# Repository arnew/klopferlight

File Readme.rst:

Klopfer Light
=============

.. figure:: ./klopferlight.png

Inspired by https://www.printables.com/model/1125977-led-cap-for-small-bottles-with-m18-thread-for-ws28 and the Mate Light https://github.com/jaseg/matelight , this design aims to provide a draft for a 4x5 crate backplane.

To be followed up with some controller and firmware design ;)

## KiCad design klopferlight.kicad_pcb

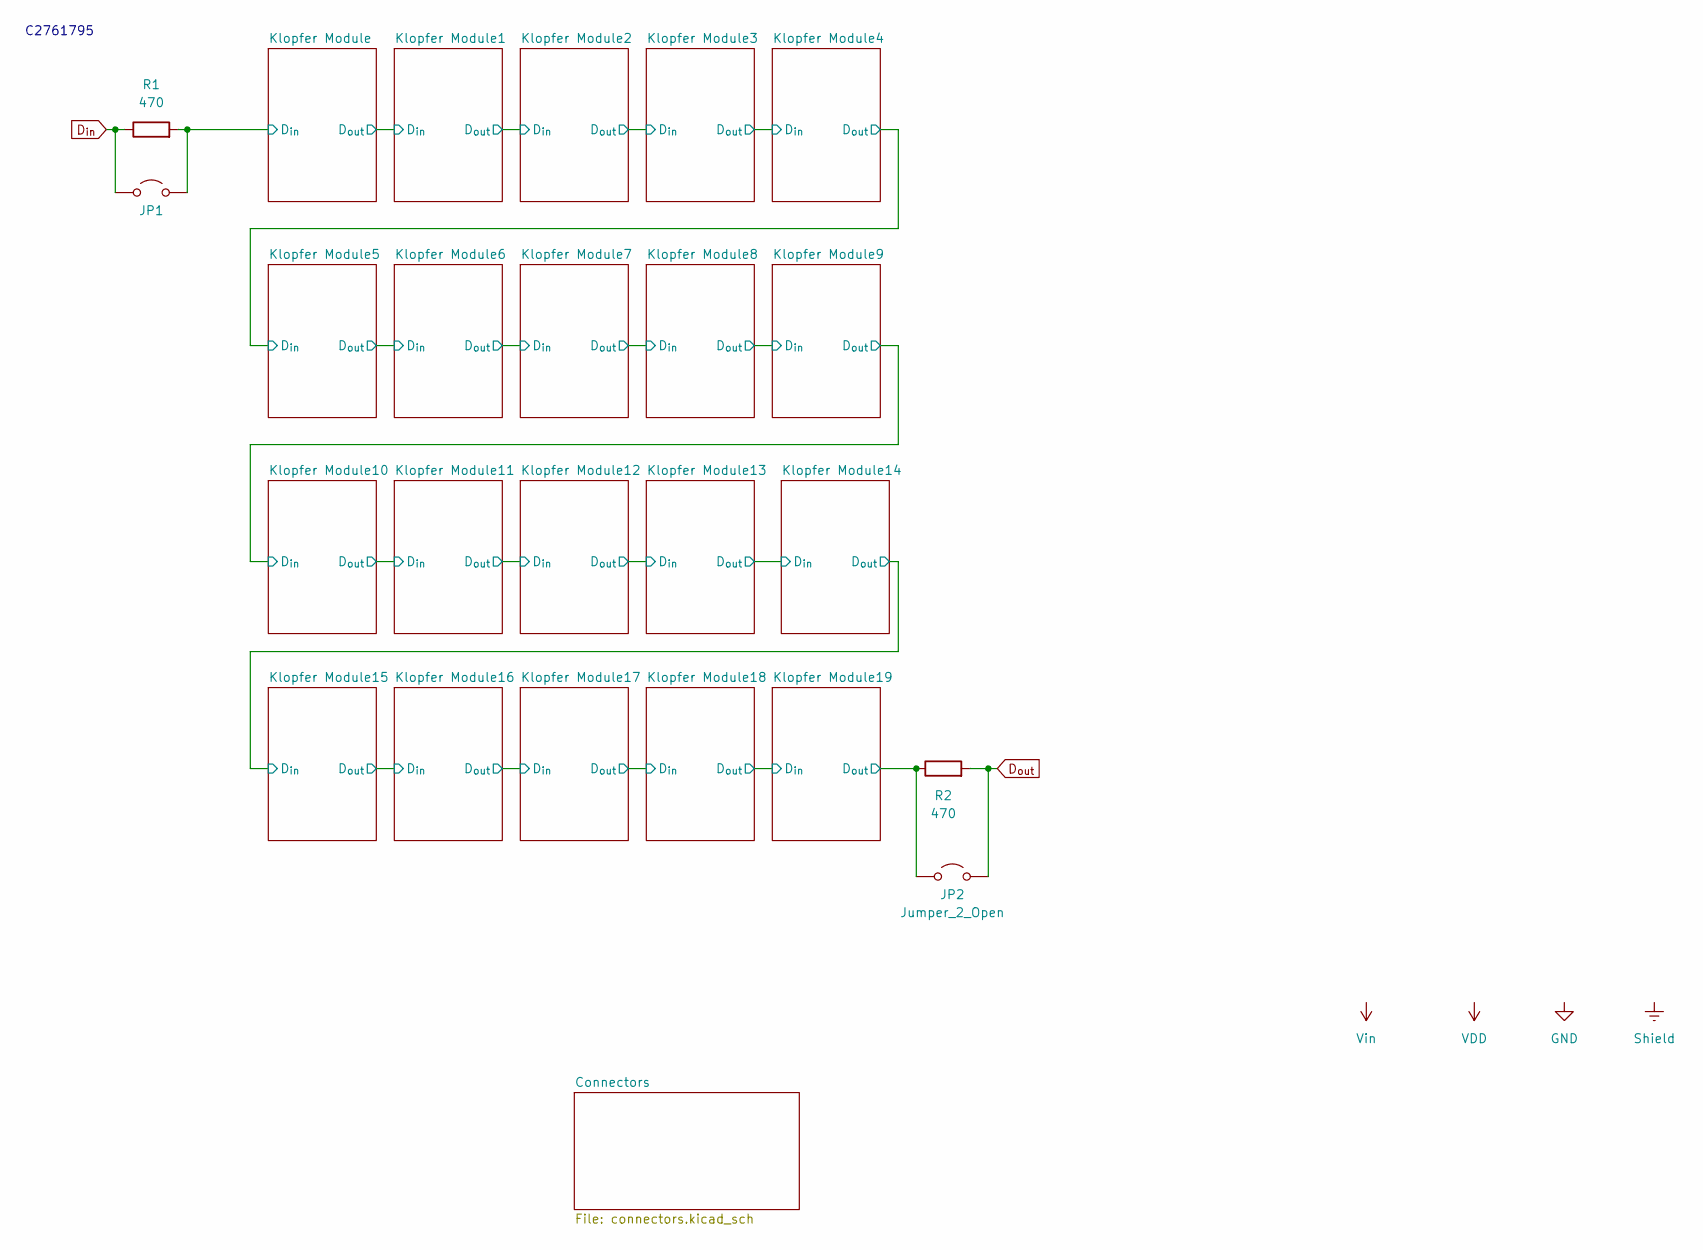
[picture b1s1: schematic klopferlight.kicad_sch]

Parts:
JP1, JP2: Jumper_2_Open; SolderJumper-2_P1.3mm_Open_RoundedPad1.0x1.5mm
R1, R2: 470; R_0603_1608Metric; LCSC C23179

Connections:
/Klopfer Module19/D_{out}: JP2.1 (A), R2.1; also elsewhere on the board
/Klopfer Module/D_{in}: JP1.2 (B), R1.2; also elsewhere on the board
D_{in}: JP1.1 (A), R1.1; also elsewhere on the board
D_{out}: JP2.2 (B), R2.2; also elsewhere on the board

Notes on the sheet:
C2761795

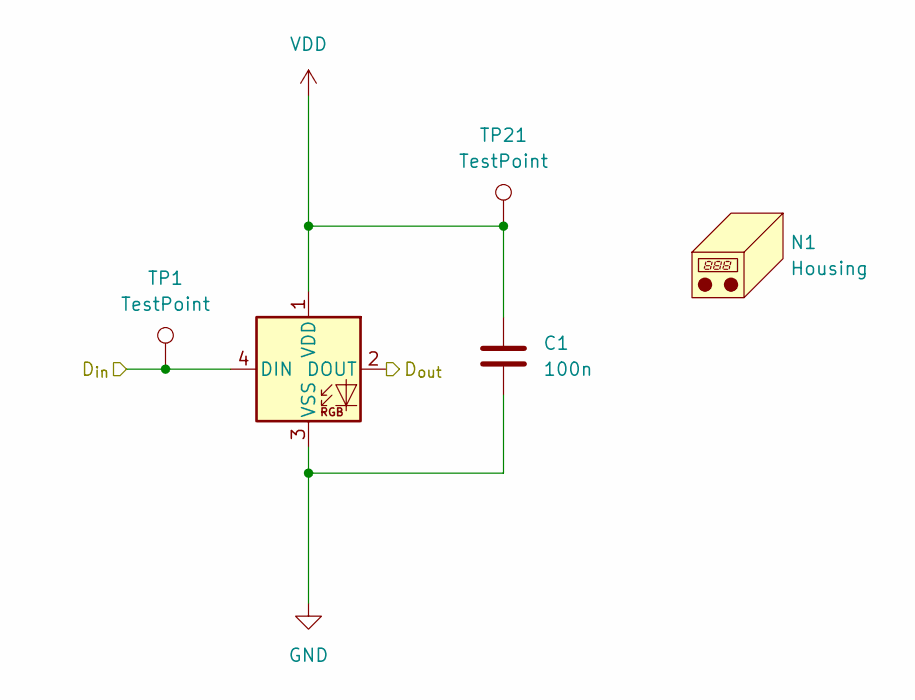
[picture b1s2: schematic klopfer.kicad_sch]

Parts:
C1: 100n; C_0603_1608Metric
D1: SK6812MINI-E; SK6812-MINI-E; LCSC C5149201
N1: Housing; klopfer
TP1, TP21: TestPoint; TestPoint_THTPad_1.0x1.0mm_Drill0.5mm

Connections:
/Klopfer Module/D_{in}: D1.4 (DIN), TP1.1; also elsewhere on the board
/Klopfer Module/D_{out}: D1.2 (DOUT); also elsewhere on the board
GND: C1.2, D1.3 (VSS); also elsewhere on the board
VDD: C1.1, D1.1 (VDD), TP21.1; also elsewhere on the board

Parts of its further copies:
C2, C3, C4, C5, C6, C7, C8, C9, C10, C11, C12, C13, C14, C15, C16, C17, C18, C19, C20: 100n; C_0603_1608Metric
D2, D3, D4, D5, D6, D7, D8, D9, D10, D11, D12, D13, D14, D15, D16, D17, D18, D19, D20: SK6812MINI-E; SK6812-MINI-E; LCSC C5149201
N2, N3, N4, N5, N6, N7, N8, N9, N10, N11, N12, N13, N14, N15, N16, N17, N18, N19, N20: Housing; klopfer
TP2, TP3, TP4, TP5, TP6, TP7, TP8, TP9, TP10, TP11, TP12, TP13, TP14, TP15, TP16, TP17, TP18, TP19, TP20, TP22, TP23, TP24, TP25, TP26, TP27, TP28, TP29, TP30, TP31, TP32, TP33, TP34, TP35, TP36, TP37, TP38, TP39, TP40: TestPoint; TestPoint_THTPad_1.0x1.0mm_Drill0.5mm

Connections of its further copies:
/Klopfer Module1/D_{out}: D2.2 (DOUT), D3.4 (DIN), TP3.1
/Klopfer Module2/D_{out}: D3.2 (DOUT), D4.4 (DIN), TP4.1
/Klopfer Module3/D_{out}: D4.2 (DOUT), D5.4 (DIN), TP5.1
/Klopfer Module4/D_{out}: D5.2 (DOUT), D6.4 (DIN), TP6.1
/Klopfer Module5/D_{out}: D6.2 (DOUT), D7.4 (DIN), TP7.1
/Klopfer Module6/D_{out}: D7.2 (DOUT), D8.4 (DIN), TP8.1
/Klopfer Module7/D_{out}: D8.2 (DOUT), D9.4 (DIN), TP9.1
/Klopfer Module8/D_{out}: D9.2 (DOUT), D10.4 (DIN), TP10.1
/Klopfer Module10/D_{in}: D10.2 (DOUT), D11.4 (DIN), TP11.1
/Klopfer Module10/D_{out}: D11.2 (DOUT), D12.4 (DIN), TP12.1
/Klopfer Module11/D_{out}: D12.2 (DOUT), D13.4 (DIN), TP13.1
/Klopfer Module12/D_{out}: D13.2 (DOUT), D14.4 (DIN), TP14.1
/Klopfer Module13/D_{out}: D14.2 (DOUT), D15.4 (DIN), TP15.1
/Klopfer Module14/D_{out}: D15.2 (DOUT), D16.4 (DIN), TP16.1
/Klopfer Module15/D_{out}: D16.2 (DOUT), D17.4 (DIN), TP17.1
/Klopfer Module16/D_{out}: D17.2 (DOUT), D18.4 (DIN), TP18.1
/Klopfer Module17/D_{out}: D18.2 (DOUT), D19.4 (DIN), TP19.1
/Klopfer Module18/D_{out}: D19.2 (DOUT), D20.4 (DIN), TP20.1
/Klopfer Module19/D_{out}: D20.2 (DOUT); also elsewhere on the board
/Klopfer Module/D_{out}: D2.4 (DIN), TP2.1; also elsewhere on the board
GND: C2.2, C3.2, C4.2, C5.2, C6.2, C7.2, C8.2, C9.2, C10.2, C11.2, C12.2, C13.2, C14.2, C15.2, C16.2, C17.2, C18.2, C19.2, C20.2, D2.3 (VSS), D3.3 (VSS), D4.3 (VSS), D5.3 (VSS), D6.3 (VSS), D7.3 (VSS), D8.3 (VSS), D9.3 (VSS), D10.3 (VSS), D11.3 (VSS), D12.3 (VSS), D13.3 (VSS), D14.3 (VSS), D15.3 (VSS), D16.3 (VSS), D17.3 (VSS), D18.3 (VSS), D19.3 (VSS), D20.3 (VSS); also elsewhere on the board
VDD: C2.1, C3.1, C4.1, C5.1, C6.1, C7.1, C8.1, C9.1, C10.1, C11.1, C12.1, C13.1, C14.1, C15.1, C16.1, C17.1, C18.1, C19.1, C20.1, D2.1 (VDD), D3.1 (VDD), D4.1 (VDD), D5.1 (VDD), D6.1 (VDD), D7.1 (VDD), D8.1 (VDD), D9.1 (VDD), D10.1 (VDD), D11.1 (VDD), D12.1 (VDD), D13.1 (VDD), D14.1 (VDD), D15.1 (VDD), D16.1 (VDD), D17.1 (VDD), D18.1 (VDD), D19.1 (VDD), D20.1 (VDD), TP22.1, TP23.1, TP24.1, TP25.1, TP26.1, TP27.1, TP28.1, TP29.1, TP30.1, TP31.1, TP32.1, TP33.1, TP34.1, TP35.1, TP36.1, TP37.1, TP38.1, TP39.1, TP40.1; also elsewhere on the board

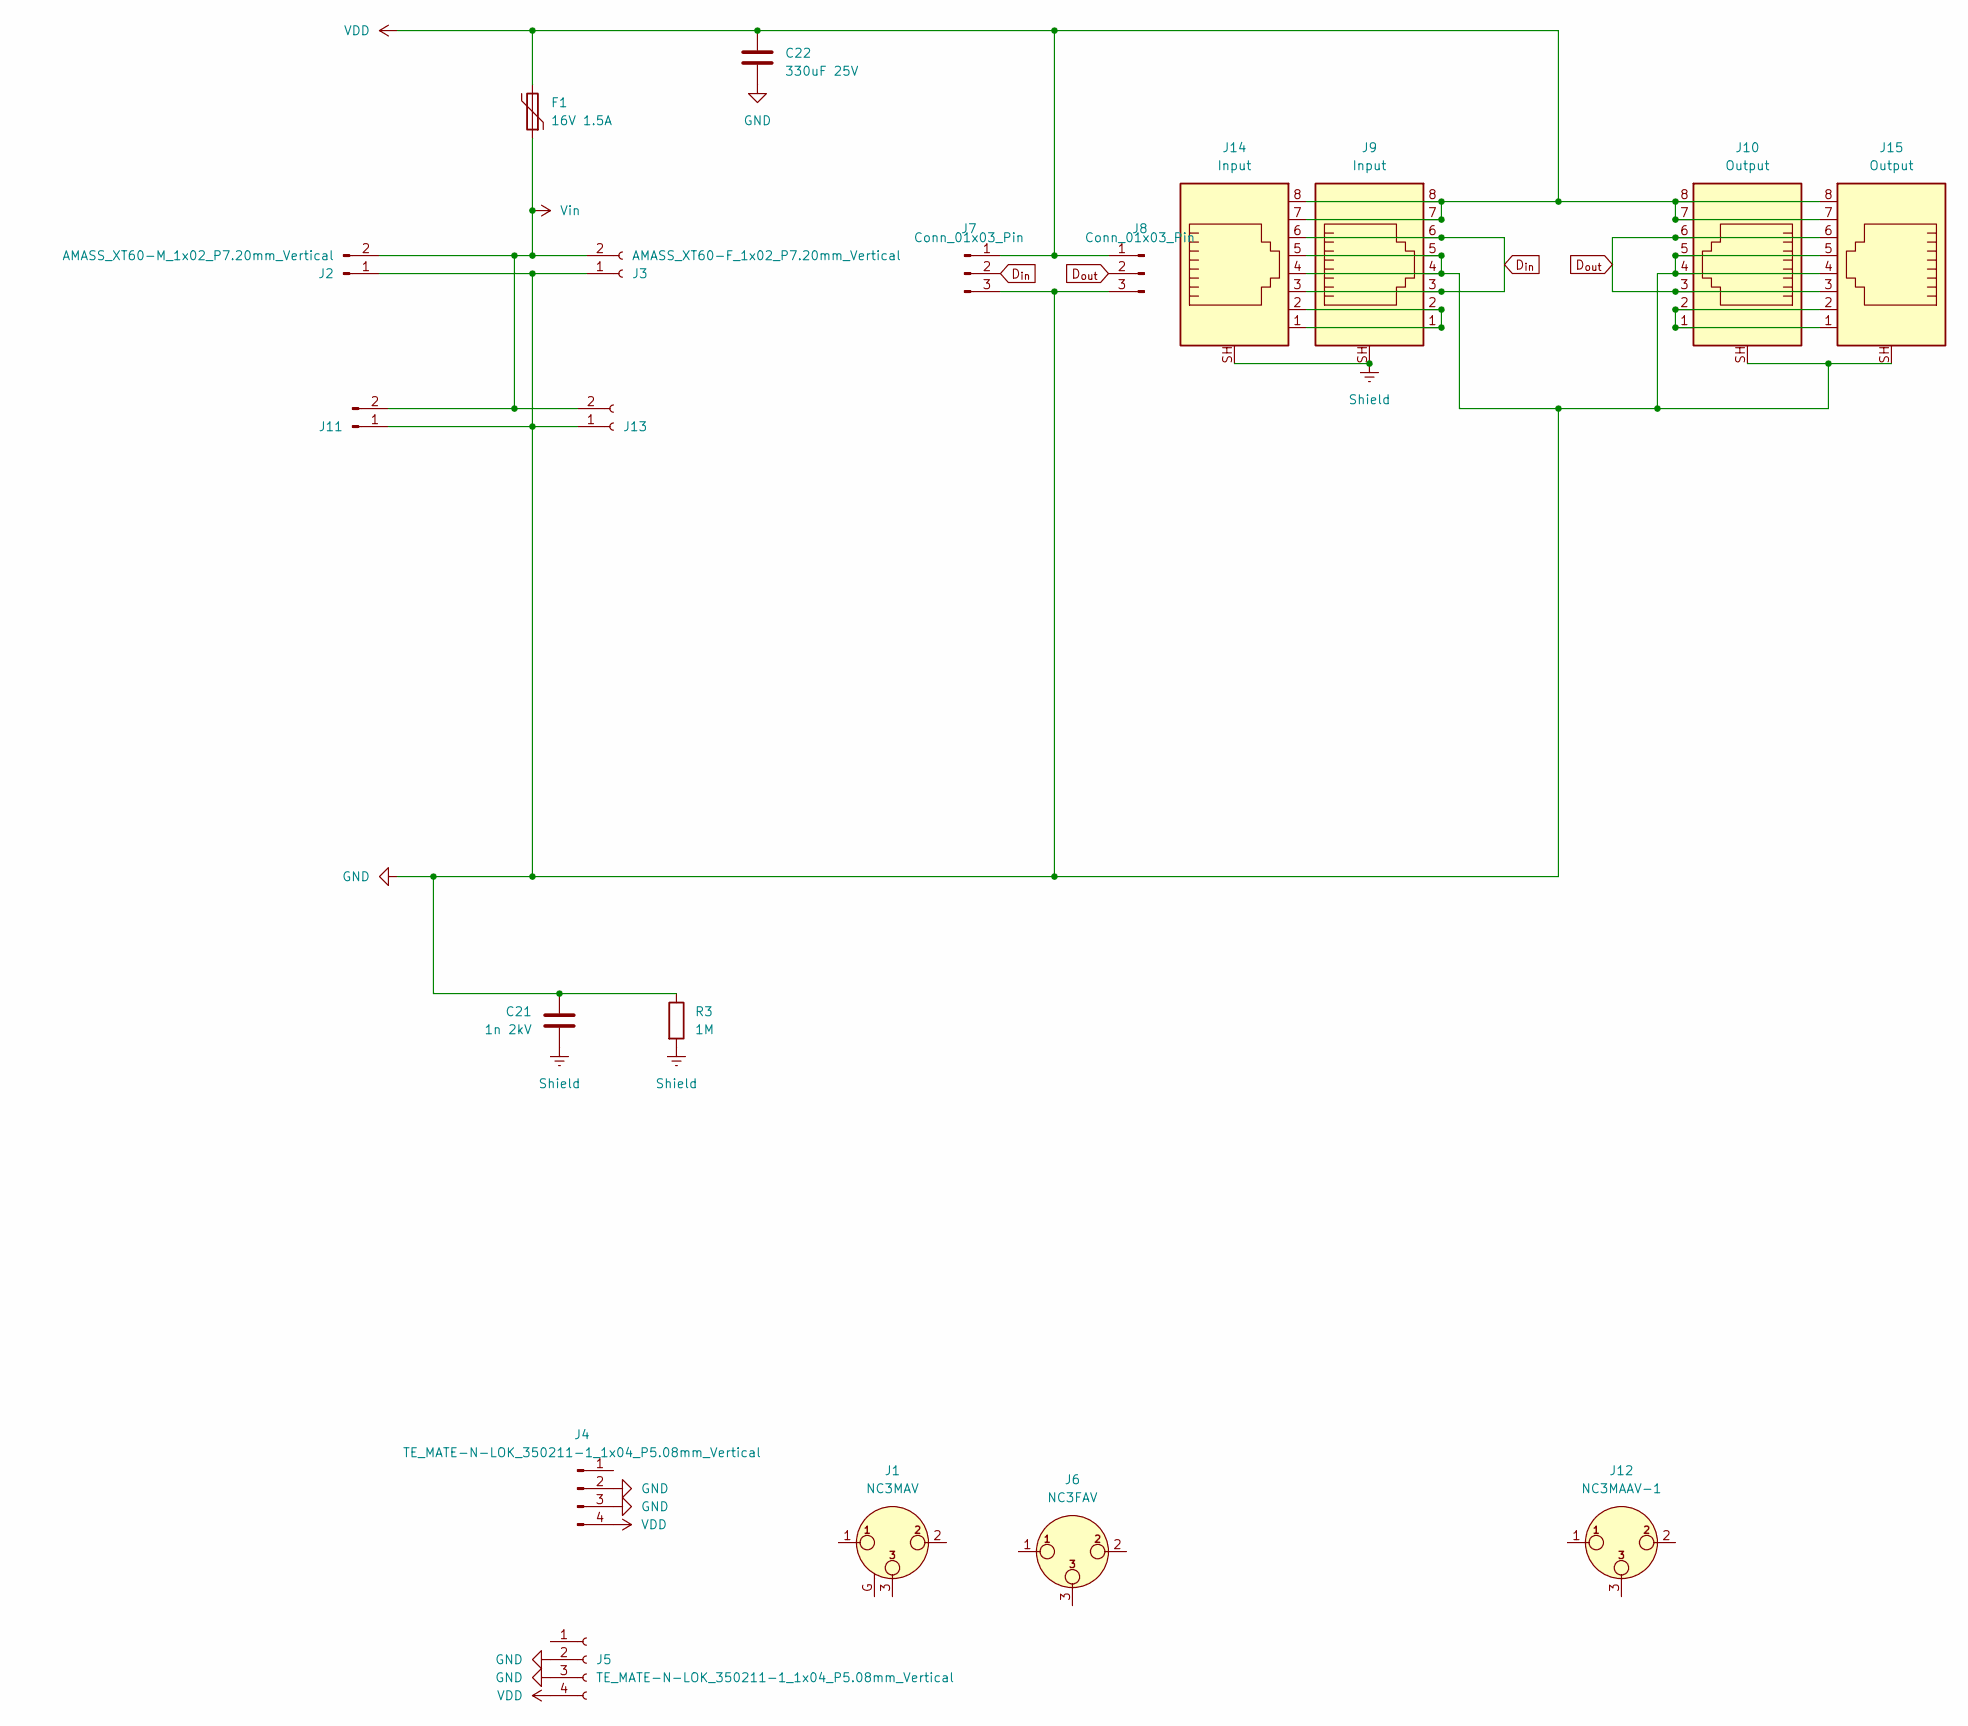
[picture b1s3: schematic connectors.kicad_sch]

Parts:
C21: 1n 2kV; C_1206_3216Metric; LCSC C9196
C22: 330uF 25V; CP_Elec_8x10.5; LCSC C74593
F1: 16V 1.5A; Fuse_1206_3216Metric; LCSC C883133
J1: NC3MAV; Jack_XLR_Neutrik_NC3MAV_Vertical; LCSC C309323
J2: AMASS_XT60-M_1x02_P7.20mm_Vertical; LCSC C98733
J3: AMASS_XT60-F_1x02_P7.20mm_Vertical; LCSC C98734
J4: TE_MATE-N-LOK_350211-1_1x04_P5.08mm_Vertical; LCSC C305826
J5: TE_MATE-N-LOK_350211-1_1x04_P5.08mm_Vertical; LCSC C305819
J6: NC3FAV; Jack_XLR_Neutrik_NC3FAV_Vertical; LCSC C309304
J7, J8: Conn_01x03_Pin; JST_XH_B3B-XH-AM_1x03_P2.50mm_Vertical; LCSC C144394
J9: Input; RJ45_Ninigi_GE; LCSC C386758
J10: Output; RJ45_Ninigi_GE; LCSC C386758
J11: AMASS_XT60PW-M_1x02_P7.20mm_Horizontal; LCSC C98732
J12: NC3MAAV-1; Jack_XLR_Neutrik_NC3MAAV-1_Vertical; LCSC C309311
J13: AMASS_XT60PW-F_1x02_P7.20mm_Horizontal; LCSC C428722
J14: Input; RJ45_RCH_RC01937; LCSC C708652
J15: Output; RJ45_RCH_RC01937; LCSC C708652
R3: 1M; R_0603_1608Metric

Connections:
D_{in}: J7.2, J9.3, J9.6, J14.3, J14.6; also elsewhere on the board
D_{out}: J8.2, J10.3, J10.6, J15.3, J15.6; also elsewhere on the board
GND: C21.2, C22.2, J2.1, J3.1, J4.2, J4.3, J5.2, J5.3, J7.3, J8.3, J9.4, J9.5, J10.4, J10.5, J10.SH, J11.1, J13.1, J14.4, J14.5, J15.4, J15.5, J15.SH, R3.1; also elsewhere on the board
unnamed: J9.1, J9.2, J14.1, J14.2
unnamed: J10.1, J10.2, J15.1, J15.2
Shield: C21.1, J9.SH, J14.SH, R3.2
VDD: C22.1, F1.2, J4.4, J5.4, J7.1, J8.1, J9.7, J9.8, J10.7, J10.8, J14.7, J14.8, J15.7, J15.8; also elsewhere on the board
Vin: F1.1, J2.2, J3.2, J11.2, J13.2

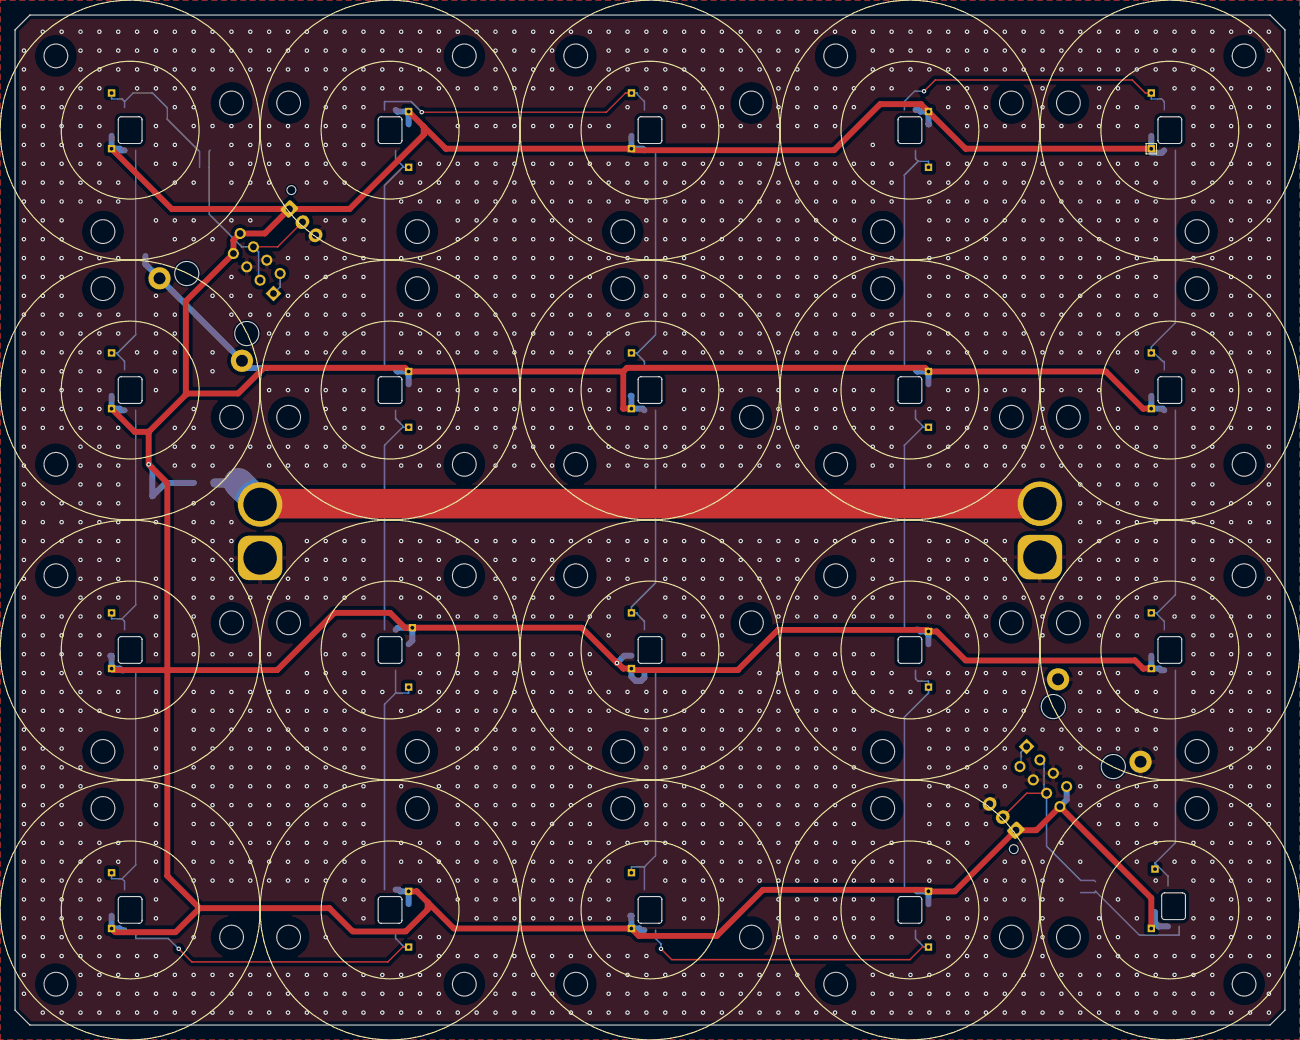
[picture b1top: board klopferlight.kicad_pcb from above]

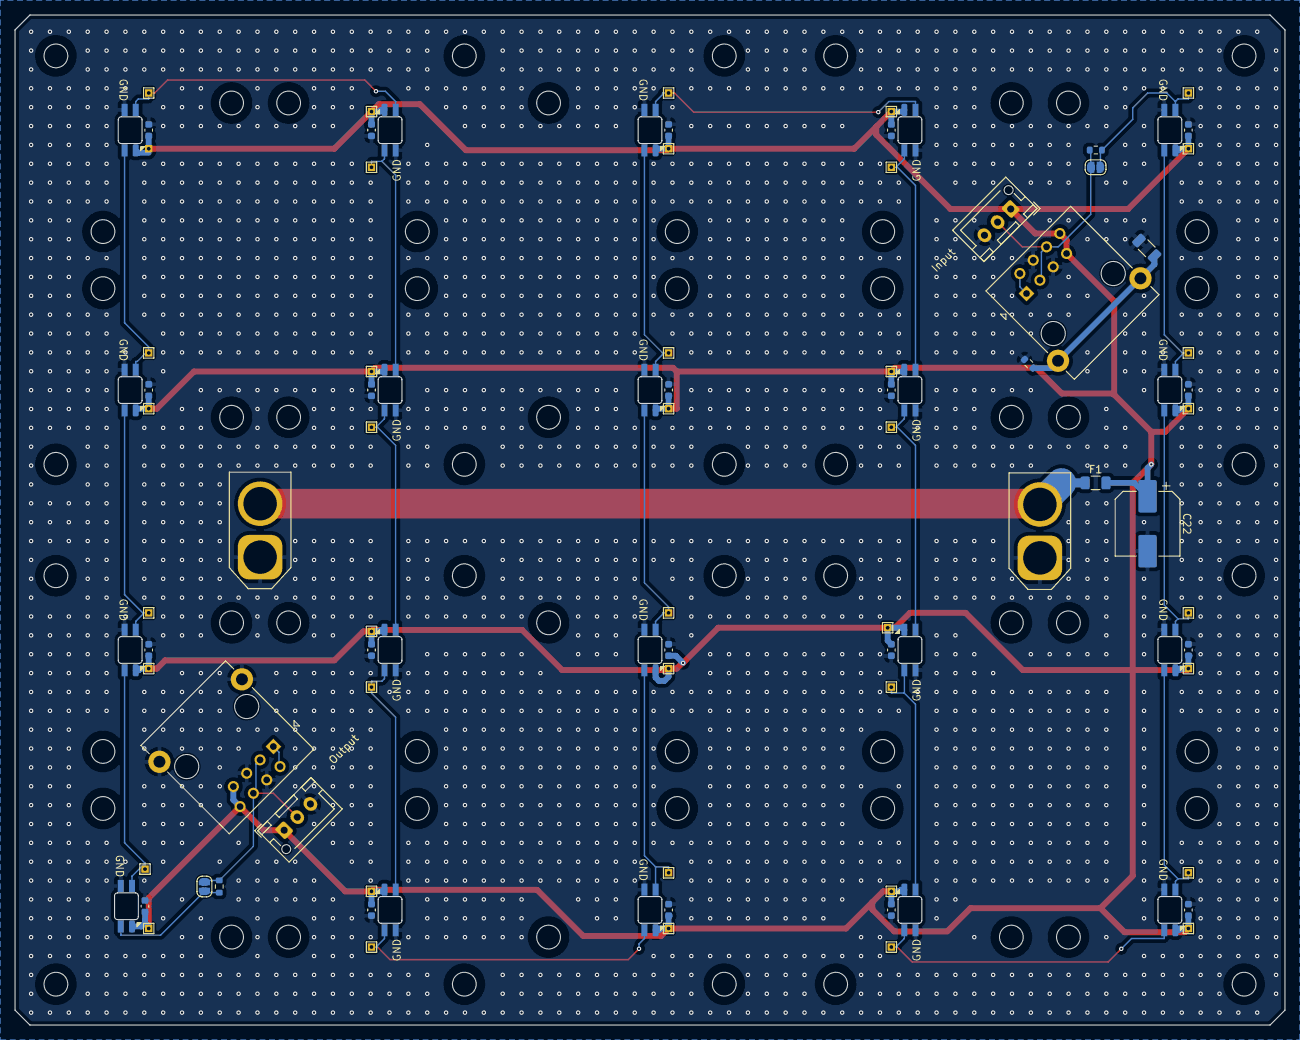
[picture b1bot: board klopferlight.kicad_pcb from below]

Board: 2 copper layers, 171.0 x 136.0 mm, 114 parts (93 on the bottom side), 29 nets.

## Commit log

2024-12-31 initial import
2024-12-31 Readme
2025-01-02 changed pcb outline
2025-09-24 snap
2025-09-24 add new footprint
